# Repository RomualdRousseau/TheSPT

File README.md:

# TheSPT
The Steam Punk RC Transmitter

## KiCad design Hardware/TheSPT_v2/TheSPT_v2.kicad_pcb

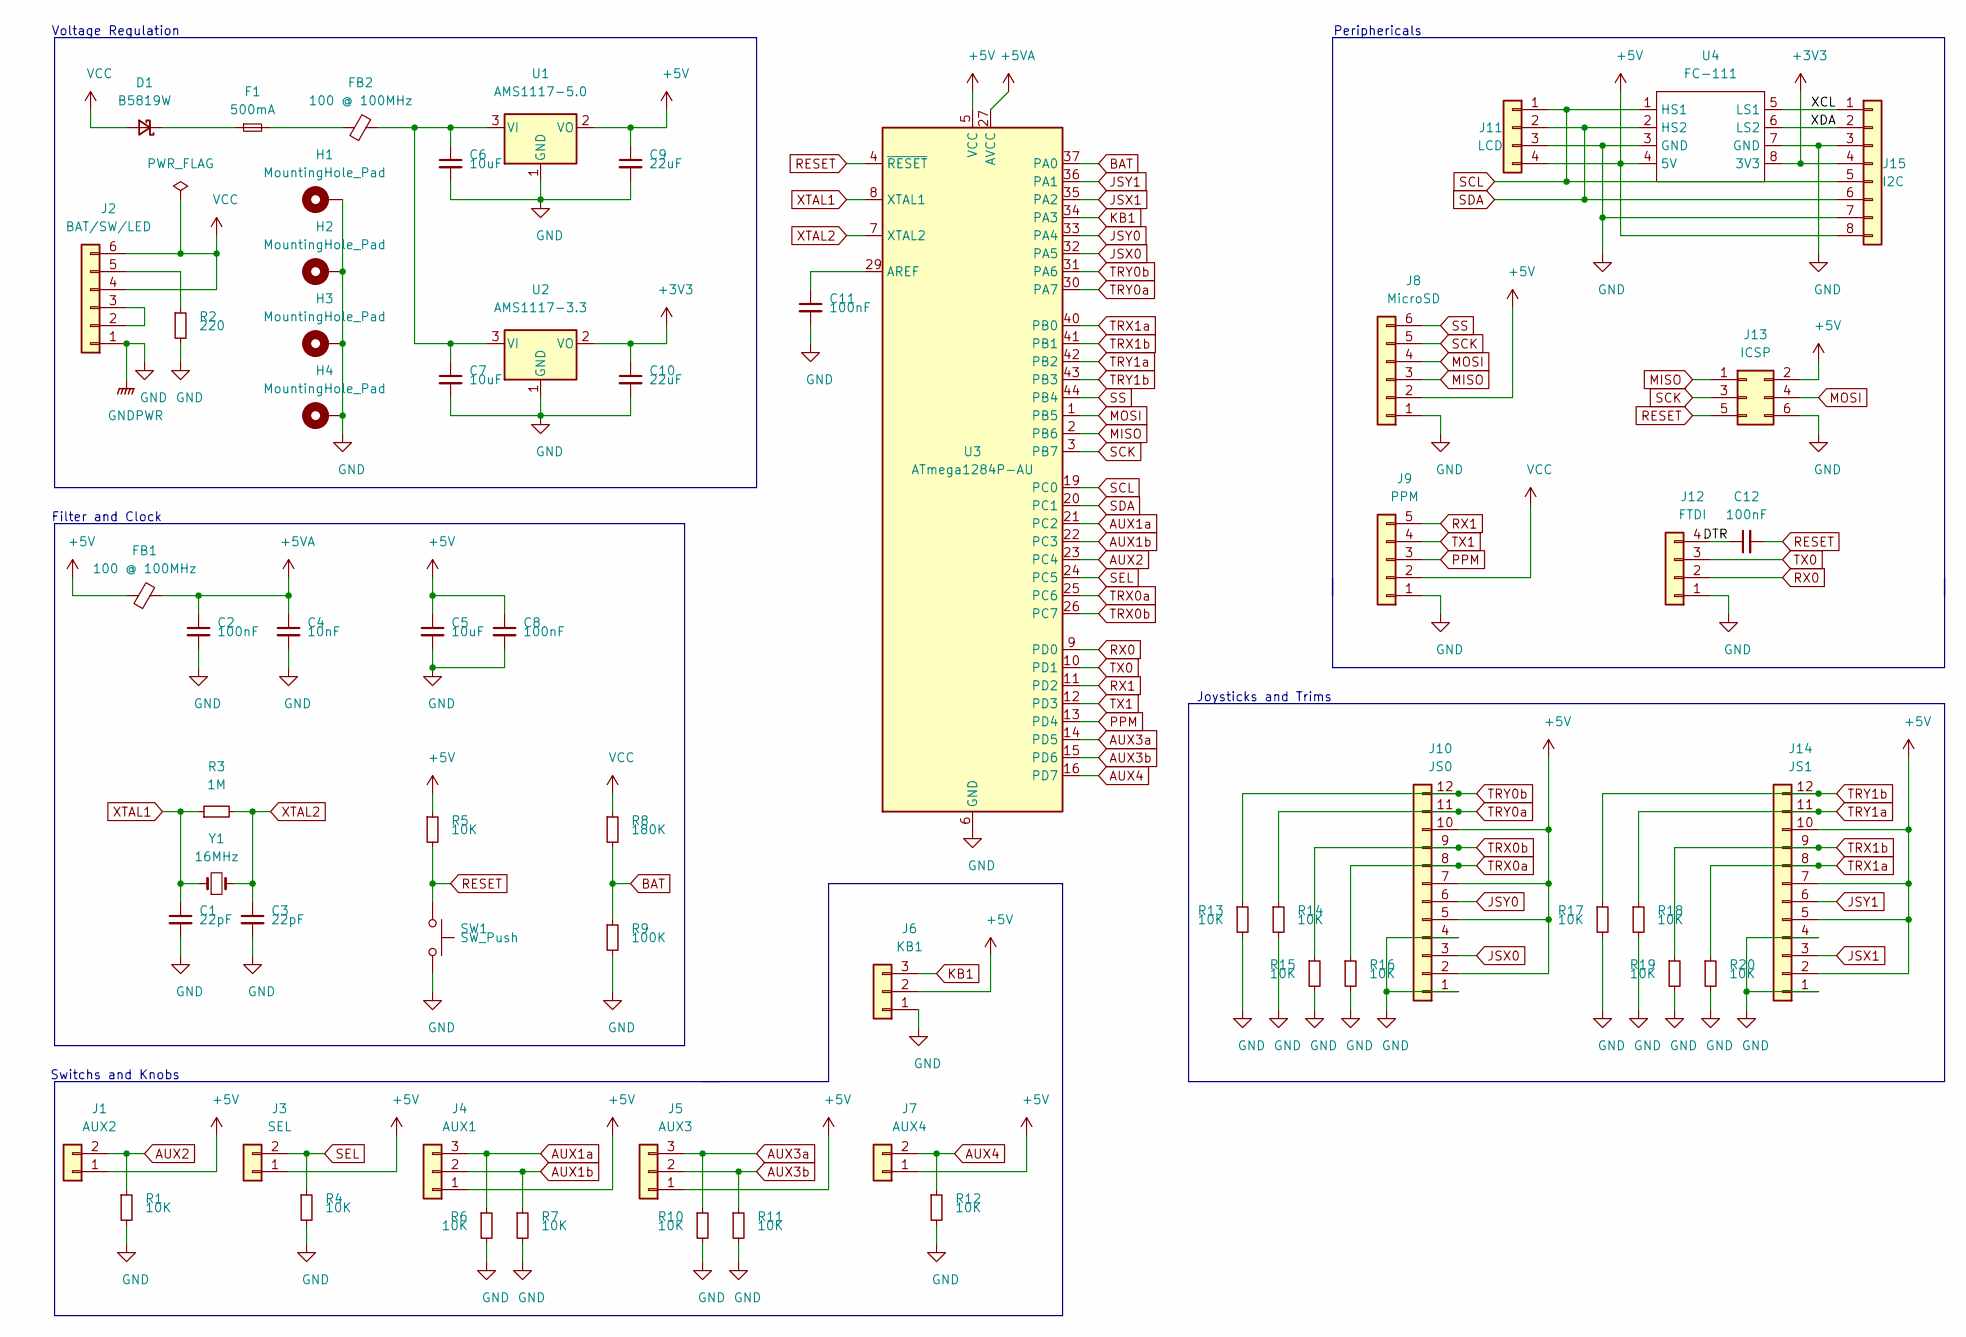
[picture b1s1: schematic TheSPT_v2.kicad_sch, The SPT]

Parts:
C1, C3: 22pF; C_0603_1608Metric
C2, C8, C11, C12: 100nF; C_0603_1608Metric
C4: 10nF; C_0603_1608Metric
C5: 10uF; C_0603_1608Metric
C6, C7: 10uF; C_0805_2012Metric
C9, C10: 22uF; C_0805_2012Metric
D1: B5819W; D_0603_1608Metric
F1: 500mA; Fuse_0603_1608Metric
FB1, FB2: 100 @ 100MHz; L_0805_2012Metric
H1, H2, H3, H4: MountingHole_Pad; MountingHole_3.2mm_M3
J1: AUX2; Molex_PicoBlade_53261-0271_1x02-1MP_P1.25mm_Horizontal
J2: BAT/SW/LED; PinHeader_1x06_P2.54mm_Vertical
J3: SEL; Molex_PicoBlade_53261-0271_1x02-1MP_P1.25mm_Horizontal
J4: AUX1; Molex_PicoBlade_53261-0371_1x03-1MP_P1.25mm_Horizontal
J5: AUX3; Molex_PicoBlade_53261-0371_1x03-1MP_P1.25mm_Horizontal
J6: KB1; Molex_PicoBlade_53261-0371_1x03-1MP_P1.25mm_Horizontal
J7: AUX4; Molex_PicoBlade_53261-0271_1x02-1MP_P1.25mm_Horizontal
J8: MicroSD; PinHeader_1x06_P2.54mm_Vertical
J9: PPM; Molex_PicoBlade_53261-0571_1x05-1MP_P1.25mm_Horizontal
J10: JS0; Molex_PicoBlade_53261-1271_1x12-1MP_P1.25mm_Horizontal
J11: LCD; Molex_PicoBlade_53261-0471_1x04-1MP_P1.25mm_Horizontal
J12: FTDI; PinHeader_1x04_P2.54mm_Vertical
J13: ICSP; PinHeader_2x03_P2.54mm_Vertical
J14: JS1; Molex_PicoBlade_53261-1271_1x12-1MP_P1.25mm_Horizontal
J15: I2C; Molex_PicoBlade_53261-0871_1x08-1MP_P1.25mm_Horizontal
R1, R4, R5, R6, R7, R10, R11, R12, R13, R14, R15, R16, R17, R18, R19, R20: 10K; R_0603_1608Metric
R2: 220; R_0603_1608Metric
R3: 1M; R_0603_1608Metric
R8: 180K; R_0603_1608Metric
R9: 100K; R_0603_1608Metric
SW1: SW_Push; SW_SPST_PTS645
U1: AMS1117-5.0; SOT-223-3_TabPin2
U2: AMS1117-3.3; SOT-223-3_TabPin2
U3: ATmega1284P-AU; TQFP-44_10x10mm_P0.8mm
U4: FC-111
Y1: 16MHz; Crystal_SMD_0603-2Pin_6.0x3.5mm

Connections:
+3V3: C10.1, J15.4, U2.2 (VO), U4.8 (3V3)
+5V: C5.1, C8.1, C9.1, FB1.1, J1.1, J3.1, J4.1, J5.1, J6.2, J7.1, J8.2, J10.2, J10.5, J10.7, J10.10, J11.4, J13.2, J14.2, J14.5, J14.7, J14.10, J15.8, R5.1, U1.2 (VO), U3.5 (VCC), U3.17 (VCC), U3.38 (VCC), U4.4 (5V)
+5VA: C2.1, C4.1, FB1.2, U3.27 (AVCC)
/DTR: C12.1, J12.4
/XCL: J15.1, U4.5 (LS1)
/XDA: J15.2, U4.6 (LS2)
AUX1a: J4.3, R6.1, U3.21 (PC2)
AUX1b: J4.2, R7.1, U3.22 (PC3)
AUX2: J1.2, R1.1, U3.23 (PC4)
AUX3a: J5.3, R10.1, U3.14 (PD5)
AUX3b: J5.2, R11.1, U3.15 (PD6)
AUX4: J7.2, R12.1, U3.16 (PD7)
BAT: R8.2, R9.1, U3.37 (PA0)
GND: C1.2, C2.2, C3.2, C4.2, C5.2, C6.2, C7.2, C8.2, C9.2, C10.2, C11.2, H1.1, H2.1, H3.1, H4.1, J2.1, J6.1, J8.1, J9.1, J10.1, J10.4, J11.3, J12.1, J13.6, J14.1, J14.4, J15.3, J15.7, R1.2, R2.2, R4.2, R6.2, R7.2, R9.2, R10.2, R11.2, R12.2, R13.2, R14.2, R15.2, R16.2, R17.2, R18.2, R19.2, R20.2, SW1.2, U1.1 (GND), U2.1 (GND), U3.6 (GND), U3.18 (GND), U3.28 (GND), U3.39 (GND), U4.3 (GND), U4.7 (GND)
JSX0: J10.3, U3.32 (PA5)
JSX1: J14.3, U3.35 (PA2)
JSY0: J10.6, U3.33 (PA4)
JSY1: J14.6, U3.36 (PA1)
KB1: J6.3, U3.34 (PA3)
MISO: J8.3, J13.1, U3.2 (PB6)
MOSI: J8.4, J13.4, U3.1 (PB5)
unnamed: C6.1, C7.1, FB2.2, U1.3 (VI), U2.3 (VI)
unnamed: C11.1, U3.29 (AREF)
unnamed: D1.1 (K), F1.1
unnamed: F1.2, FB2.1
unnamed: J2.2, J2.3
unnamed: J2.5, R2.1
PPM: J9.3, U3.13 (PD4)
RESET: C12.2, J13.5, R5.2, SW1.1, U3.4 (~RESET)
RX0: J12.2, U3.9 (PD0)
RX1: J9.5, U3.11 (PD2)
SCK: J8.5, J13.3, U3.3 (PB7)
SCL: J11.1, J15.5, U3.19 (PC0), U4.1 (HS1)
SDA: J11.2, J15.6, U3.20 (PC1), U4.2 (HS2)
SEL: J3.2, R4.1, U3.24 (PC5)
SS: J8.6, U3.44 (PB4)
TRX0a: J10.8, R16.1, U3.25 (PC6)
TRX0b: J10.9, R15.1, U3.26 (PC7)
TRX1a: J14.8, R20.1, U3.40 (PB0)
TRX1b: J14.9, R19.1, U3.41 (PB1)
TRY0a: J10.11, R14.1, U3.30 (PA7)
TRY0b: J10.12, R13.1, U3.31 (PA6)
TRY1a: J14.11, R18.1, U3.42 (PB2)
TRY1b: J14.12, R17.1, U3.43 (PB3)
TX0: J12.3, U3.10 (PD1)
TX1: J9.4, U3.12 (PD3)
VCC: D1.2 (A), J2.4, J2.6, J9.2, R8.1
XTAL1: C1.1, R3.1, U3.8 (XTAL1), Y1.1
XTAL2: C3.1, R3.2, U3.7 (XTAL2), Y1.2

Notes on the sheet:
Joysticks and Trims
Periphericals
Voltage Regulation
Filter and Clock
Switchs and Knobs

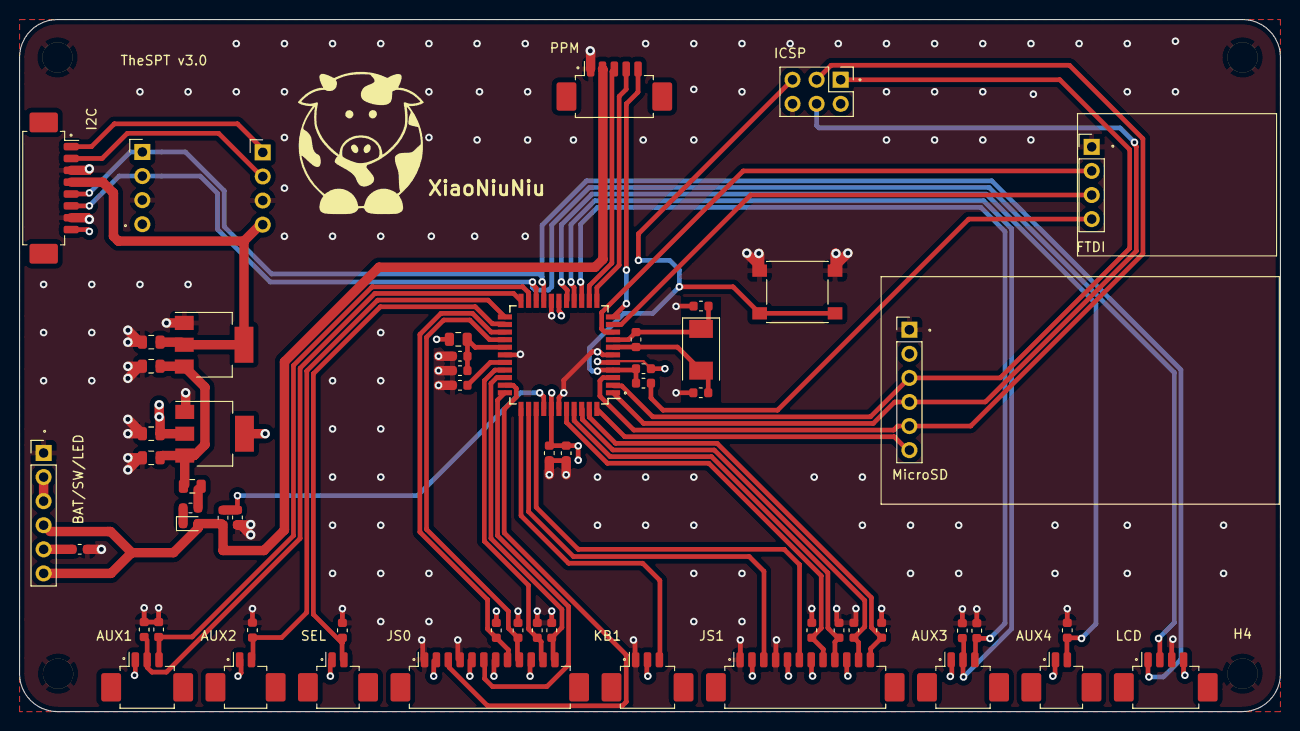
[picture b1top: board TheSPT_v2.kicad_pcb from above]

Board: 4 copper layers, 133.0 x 73.0 mm, 62 parts (0 on the bottom side), 49 nets.

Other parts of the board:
XiaoNiuNiu: LOGO; SmallCow

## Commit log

2016-05-15 Added some images
2016-10-30 New version of the mainboard; upgraded to chip to ATMega1284A and better overall design.
2016-10-30 Added some photos of the new board.
2016-10-31 Added some images for instructables.
2018-06-02 Cleanup and refactor
2018-06-02 Added Software
2018-06-02 Added Hardware
2018-06-02 Added Documentation
2020-07-08 New design and function input
2021-12-21 Remove kicad backups
2021-12-21 Cleanup backups
2021-12-21 Cleanup
